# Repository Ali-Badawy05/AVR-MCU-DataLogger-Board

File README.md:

# AVR MCU DataLogger Board

A graduation-project PCB designed in **KiCad** around the
**ATmega328P-AU** microcontroller. The board is designed as an MCU-based
data logger with persistent storage, real-time timestamping, status
indicators, and accessible communication interfaces.

## Project Overview

The board combines:

-   **ATmega328P-AU** as the main microcontroller
-   **2 × 24LC1025 I2C EEPROMs** for persistent data storage
-   **DS1337S I2C Real-Time Clock (RTC)** for timestamped logging
-   SPI, UART, I2C, and GPIO breakout headers
-   Power and SPI-clock indicator LEDs
-   Reverse-polarity protection
-   A double-layer PCB with a bottom-layer ground plane
-   Manufacturing outputs including Gerber and drill files

## Main Components

  Reference   Component                Purpose
  ----------- ------------------------ ----------------------------------
  U1          ATmega328P-AU            Main microcontroller
  U2, U3      24LC1025 ×2              I2C EEPROM data storage
  U4          DS1337S                  Real-time clock for timestamping
  Y1          16 MHz crystal           MCU clock
  Y2          32.768 kHz crystal       RTC clock
  D4          Power LED                Power indication
  D5          SPI-clock LED            SPI clock activity indication
  D7          Reverse-polarity diode   Power protection
  SW1         Push button              MCU reset
  J1          Power connector          Board power input
  J2          SPI header               SPI interface
  J3          UART header              UART interface
  J4          I2C header               I2C interface
  J6          GPIO header              GPIO breakout

## Key Design Features

### Microcontroller

The central controller is the **ATmega328P-AU**, using an external **16
MHz crystal**.

The MCU section includes:

-   External clock circuit
-   Reset push button
-   10 kΩ reset pull-up
-   AREF filtering

### Data Storage

Two **24LC1025** EEPROM devices are connected to the I2C bus.

-   2 EEPROM chips
-   128 KB per chip
-   Used for persistent data logging

### Real-Time Clock

The **DS1337S** provides real-time information for timestamping logged
data.

It uses a dedicated **32.768 kHz crystal** and communicates through the
same I2C bus as the EEPROMs.

### Interfaces

The PCB provides dedicated breakout headers for:

-   **SPI**
-   **UART**
-   **I2C**
-   **GPIO**

### Power & Indicators

The power section includes:

-   Power input connector
-   Reverse-polarity protection
-   10 µF bulk capacitor
-   Power LED
-   SPI-clock activity LED

The I2C bus uses shared **4.7 kΩ pull-up resistors**.

## PCB Design

The PCB is a **double-layer board** with functional component placement
and routed traces.

Design details:

-   MCU placed centrally
-   EEPROMs and RTC arranged to reduce unwanted coupling
-   0.2 mm signal traces
-   Bottom-layer GND plane
-   14 vias
-   DRC verification completed
-   Zero DRC violations
-   Zero unconnected nets

The project documentation states that the 0.2 mm signal traces were
checked against IPC-2221 for the board's stated load of less than 200
mA.

## Repository Structure

A clean GitHub repository can be organized as follows:

``` text
AVR-microcontroller/
│
├── README.md
│
├── KiCad/
│   ├── AVR_microcontroller.kicad_pro
│   ├── AVR_microcontroller.kicad_sch
│   ├── AVR_microcontroller.kicad_pcb
│   ├── DS1337S.pretty/
│   └── Connectors/
│
├── Gerbers/
│   ├── Gerber files...
│   └── Drill files...
│
├── Documentation/
│   └── presentation.pdf
│
└── .gitignore
```

## Files Not Recommended for GitHub

The following are local/generated files and normally should not be
included:

``` text
.history/
pcb_logs.pretty/
*_pro.lck
*.kicad_prl
```

The `.kicad_prl` file contains local KiCad settings, while the lock file
is temporary. The history/log folders are also not required to reproduce
the PCB design.

## Manufacturing Files

The repository includes the generated **Gerber and drill files**
required for PCB fabrication.

These files are kept separately from the editable KiCad design files so
that the repository contains both:

1.  The original editable PCB project
2.  The manufacturing-ready output files
## Tools

-   **KiCad 10**
-   PCB schematic and layout design
-   Gerber/drill generation
-   Design Rules Check (DRC)

## Project Status

-   [x] Schematic completed
-   [x] PCB layout completed
-   [x] DRC completed
-   [x] Zero unconnected nets
-   [x] Gerber files generated
-   [x] Drill files generated
-   [x] 3D board render completed

## Author
Aly Badawy

**Aly Badawy**\
IMT School

------------------------------------------------------------------------

*AVR MCU DataLogger Board --- Graduation Project*

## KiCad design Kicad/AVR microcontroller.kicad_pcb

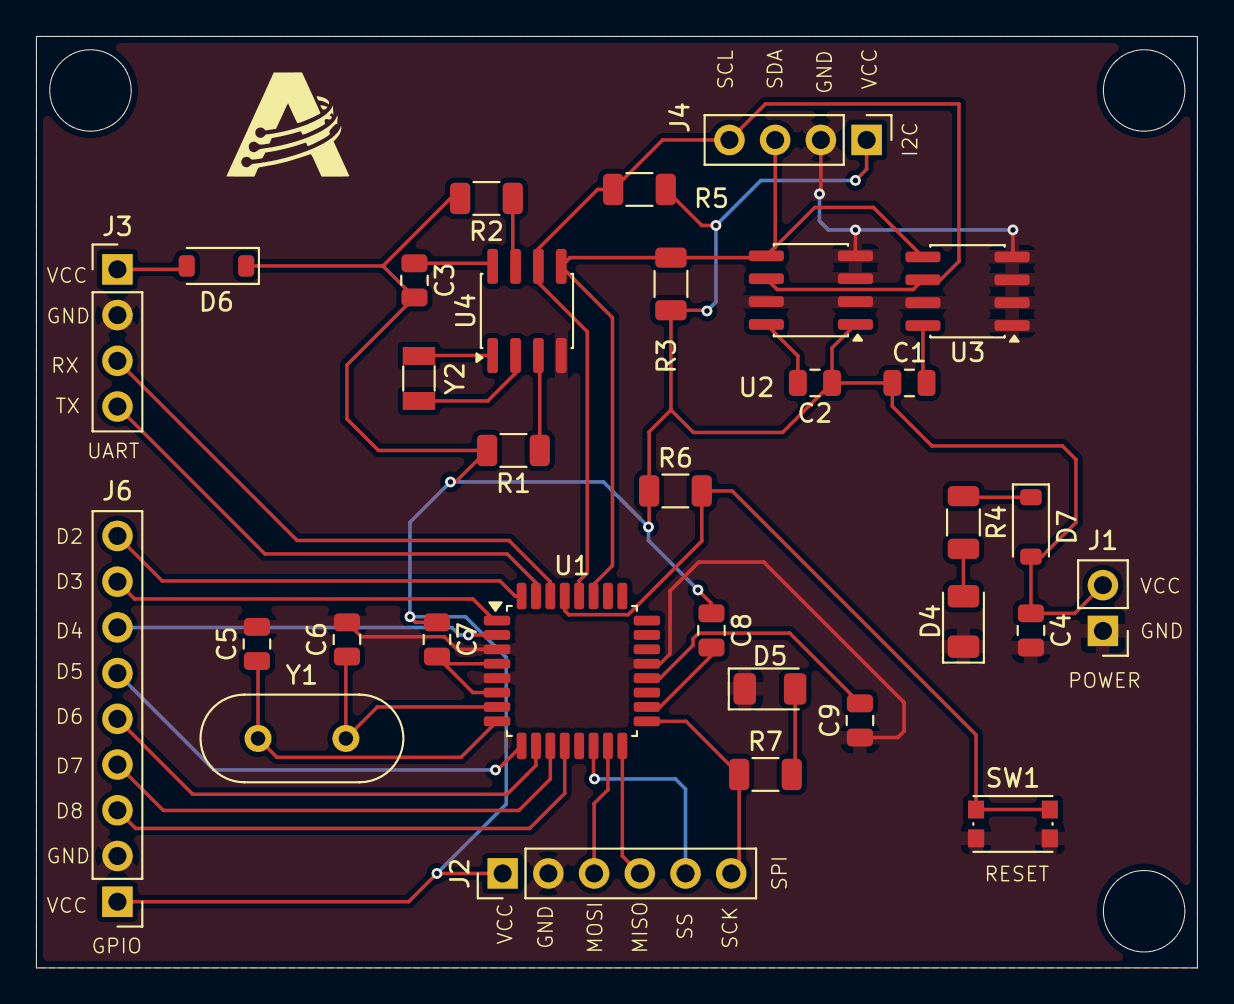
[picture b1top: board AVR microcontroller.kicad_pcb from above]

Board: 2 copper layers, 64.5 x 51.8 mm, 32 parts (0 on the bottom side), 34 nets.

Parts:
C1, C2, C3, C7, C8: 0.1µF; C_0805_2012Metric
C4: 10µF; C_0805_2012Metric
C5, C6: 22pF; C_0805_2012Metric
C9: 100nF; C_0805_2012Metric
D4: LED-power; LED_1206_3216Metric
D5: LED-SCK; LED_1206_3216Metric
D6: BAV16W uart; D_SOD-123
D7: BAV16W power; D_SOD-123
J1: POWER CONNECTOR; PinHeader_1x02_P2.54mm_Vertical
J2: Conn_SPI; PinHeader_1x06_P2.54mm_Vertical
J3: Conn_UART; PinHeader_1x04_P2.54mm_Vertical
J4: Conn_I2C; PinHeader_1x04_P2.54mm_Vertical
J6: Conn_01x09_Pin; PinHeader_1x09_P2.54mm_Vertical
R1, R2, R6: 10kΩ; R_1206_3216Metric
R3, R5: 4.7kΩ; R_1206_3216Metric
R4: 330Ω; R_1206_3216Metric
R7: 1kΩ; R_1206_3216Metric
SW1: SW_SPST; SW_Push_1P1T_NO_CK_KMR2
U1: ATmega328P-A; TQFP-32_7x7mm_P0.8mm
U2, U3: 24LC1025; SOIC-8_3.9x4.9mm_P1.27mm
U4: DS1337S_; SOIC-8_3.9x4.9mm_P1.27mm
Y1: Crystal; Crystal_HC49-4H_Vertical
Y2: 32Hz; Crystal_SMD_3215-2Pin_3.2x1.5mm

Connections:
/MISO: J2.4, U1.16 (PB4)
/MOSI: J2.3, U1.15 (PB3)
/RST: R6.2, SW1.2 (B), U1.29 (~RESET/PC6)
/RXD: J3.3, U1.30 (PD0)
/SCK: J2.6, R7.1, U1.17 (PB5)
/SCL: J4.4, R5.1, U1.28 (PC5), U2.6 (SCL), U3.6 (SCL), U4.6 (SCL)
/SDA: J4.3, R3.1, U1.27 (PC4), U2.5 (SDA), U3.5 (SDA), U4.5 (SDA)
/SS: J2.5, U1.14 (PB2)
/TXD: J3.4, U1.31 (PD1)
/XTAL1: C6.1, U1.7 (XTAL1/PB6), Y1.2
/XTAL2: C5.1, U1.8 (XTAL2/PB7), Y1.1
GND: C4.2, C5.2, C6.2, C9.1, D4.1 (K), D5.1 (K), J1.1, J2.2, J3.2, J4.2, J6.2, SW1.1 (A), U1.3 (GND), U1.5 (GND), U1.21 (GND), U2.2 (A1), U2.3 (A2), U2.4 (GND), U2.7 (WP), U3.1 (A0), U3.2 (A1), U3.3 (A2), U3.4 (GND), U3.7 (WP), U4.4 (GND)
unnamed: C7.2, U1.4 (VCC), U1.6 (VCC)
unnamed: D4.2 (A), R4.2
unnamed: D5.2 (A), R7.2
unnamed: D6.2 (A), J3.1
unnamed: D7.1 (K), R4.1
unnamed: J6.3, U1.12 (PB0)
unnamed: J6.4, U1.11 (PD7)
unnamed: J6.5, U1.10 (PD6)
unnamed: J6.6, U1.9 (PD5)
unnamed: J6.7, U1.2 (PD4)
unnamed: J6.8, U1.1 (PD3)
unnamed: J6.9, U1.32 (PD2)
unnamed: C9.2, U1.20 (AREF)
unnamed: C8.2, U1.18 (AVCC)
unnamed: C2.2, U2.8 (VCC)
unnamed: C1.2, U3.8 (VCC)
unnamed: R2.1, U4.7 (SQW/~INT)
unnamed: C3.1, U4.8 (VCC)
unnamed: U4.1 (X1), Y2.2
unnamed: U4.2 (X2), Y2.1
unnamed: R1.1, U4.3 (~INTA)
VCC: C1.1, C2.1, C3.2, C4.1, C7.1, C8.1, D6.1 (K), D7.2 (A), J1.2, J2.1, J4.1, J6.1, R1.2, R2.2, R3.2, R5.2, R6.1, U2.1 (A0)
